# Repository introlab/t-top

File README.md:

# T-Top

T-Top is a tabletop robot designed with advanced audio and vision sensors, deep learning perceptual processing and
telecommunication capabilities to provide richer interaction modalities and develop higher cognitive abilities from
interacting with people.

## Authors

- Marc-Antoine Maheux (@mamaheux)
- Dominic Létourneau (@doumdi)
- Philippe Warren (@philippewarren)
- Mariam Fdil (@MariamFdil)
- [François Michaud](mailto:francois.michaud@usherbrooke.ca), ing., Ph.D.

## Contributors

- Ian-Mathieu Joly (@joli-1801)
- Charles Caya (@chcaya)
- Alexandre Filion (@alexfilion)

## Licensing

- Source code files: [GPLv3](LICENSE_SOURCE_CODE)
- Other files: [Creative Commons Attribution-NonCommercial-ShareAlike 4.0 International Public License](LICENSE_OTHER)

## Features

| Category         | Type              | Description                                                                                                                                                                                                                                             |
| ---------------- | ----------------- | ------------------------------------------------------------------------------------------------------------------------------------------------------------------------------------------------------------------------------------------------------- |
| Power            | Power Adapter     | 19 V                                                                                                                                                                                                                                                    |
|                  | Battery           | 1x [RRC2054-2](https://www.rrc-ps.com/en/battery-packs/standard-battery-packs/products/RRC2054-2)                                                                                                                                                       |
|                  | Battery Charger   | 1x [RRC-PMM240](https://www.rrc-ps.com/en/battery-packs/standard-battery-packs/products/RRC-PMM240)                                                                                                                                                     |
| Sensors          | Microphone Array  | 16x [xSoundsMicrophones](https://github.com/introlab/xSoundsMicrophones), 1x [16SoundsUSB](https://github.com/introlab/16SoundsUSB)                                                                                                                     |
|                  | RGB-D Camera      | 1x [Intel RealSense D435i](https://www.intelrealsense.com/depth-camera-d435i/)                                                                                                                                                                          |
|                  | Wide Angle Camera | 1x [Arducam AR0230](https://www.uctronics.com/arducam-1080p-hd-wide-angle-wdr-usb-camera-module-for-computer-2mp-1-2-7-cmos-ar0230-100-degree-mini-uvc-usb2-0-spy-webcam-board-with-3-3ft-1m-cable-for-windows-linux-mac-os-android.html)               |
|                  | Touchscreen       | 1x 7 inch 1024x600 capacitive touchscreen                                                                                                                                                                                                               |
|                  | Current/Voltage   | [INA220](https://www.ti.com/product/INA220)                                                                                                                                                                                                             |
|                  | Light Sensors     | 4x [Adafruit ALS-PT19 ](https://www.adafruit.com/product/2748)                                                                                                                                                                                          |
|                  | Buttons           | 4x buttons                                                                                                                                                                                                                                              |
| Actuators        | Stewart Platform  | Displacement range: ±3 cm (x, y and z), ±20° (x and y), ±30° (z). Motor: [Dynamixel XL430-W250](https://emanual.robotis.com/docs/en/dxl/x/xl430-w250/)                                                                                                  |                                                         |
|                  | Rotating Base     | Displacement range: illimited. Motor: [Dynamixel XL430-W250](https://emanual.robotis.com/docs/en/dxl/x/xl430-w250/)                                                                                                                                     |
|                  | Speakers          | 4x [Dayton Audio DMA45-8](https://www.daytonaudio.com/product/1613/dma45-8-1-1-2-dual-magnet-aluminum-cone-full-range-driver-8-ohm), 2x [MAX9744](https://www.adafruit.com/product/1752)                                                                |
|                  | Cooling           | 2x [Noctua NF-A4x20 5V](https://noctua.at/en/products/fan/nf-a4x20-5v)                                                                                                                                                                                  |
|                  | Touchscreen       | 1x 7 inch 1024x600 capacitive touchscreen                                                                                                                                                                                                               |
|                  | LED               | Battery status, volume level, led strip                                                                                                                                                                                                                 |
| Network          | WiFi              | Intel Dual Band Wireless-AC 8265 NGW                                                                                                                                                                                                                    |
|                  | Ethernet          | 100 Mbps                                                                                                                                                                                                                                                |
| Processing       | Computer          | [NVIDIA Jetson AGX Xavier Developer Kit](https://developer.nvidia.com/embedded/jetson-agx-xavier-developer-kit) or [NVIDIA Jetson AGX Xavier Orin Developer Kit](https://developer.nvidia.com/embedded/jetson-agx-orin-developer-kit)                   |
|                  | Motor MCU         | [Teensy 4.0](https://www.pjrc.com/store/teensy40.html)                                                                                                                                                                                                  |
|                  | Battery MCU       | [Teensy LC](https://www.pjrc.com/teensy/teensyLC.html)                                                                                                                                                                                                  |
| Perceptions      |                   | SLAM, object detection, person pose estimation, face recognition, sound classification, speaker identification, robot name detection, speech to text, person identification, music beat detection, source source localization, ego noise reduction, vad |
| Behaviors        |                   | Telepresence, emotions, talking, greeting, face following, dancing, exploring, sound following                                                                                                                                                          |

## Repository Structure

- The [documentation](documentation) folder contains the documentation to build and configure T-Top.
- The [CAD](CAD) folder contains the SolidWorks files of the robot. Il also contains the DXF and STL files to cut and
  print custom parts.
- The [firmwares](firmwares) folder contains the firmware for the MCUs.
- The [PCB](PCB) folder contains the KiCad files of the custom PCBs. Il also contains the Gerber files to manufacture
  the PCBs.
- The [ros](ros) folder contains the ROS packages to use the robot.
- The [tools](tools) folder contains the tools to develop and use the robot.

## Development Computer Setup

See [01_COMPUTER_CONFIGURATION.md](documentation/assembly/01_COMPUTER_CONFIGURATION.md#development-computer-ubuntu-2004)

## Papers

- [M.-A. Maheux, D. Létourneau, P. Warren, A. M. Panchea, J. M. Robillard and F. Michaud, “‍Designing a Tabletop SAR as an Advanced HRI Experimentation Platform,” in Proceedings of the 2024 International Symposium on Technological Advances in Human-Robot Interaction (TAHRI 2024), Boulder, CO, USA, 2024](https://dl.acm.org/doi/10.1145/3648536.3648538)
    - [YouTube Video](https://youtu.be/HSd65F055VE)
- [M. Fdil, M. Levasseur, D. Létourneau, M.-A. Maheux, M. Lussier-Therrien, F. Michaud, "Enhancing Open Conversations Using Visual Percepts From a Socially Assistive Robot -- Preliminary Assessment", in Proceedings of the International Conference on Social Robotics, 2024, pp. 1-12.](https://link.springer.com/chapter/10.1007/978-981-96-3519-1_17)
    - [YouTube Video](https://youtu.be/4ykoxQKUweU)  
- [A. M. Panchea, M.-A. Maheux, P. Warren, D. Létourneau and F. Michaud, “Exploratory Evaluation of a Tabletop Robot With Older Adults,” in Proceedings of the 2024 ACM/IEEE International Conference on Human-Robot Interaction, Boulder, CO, USA, 2024, pp. 817–821.](https://dl.acm.org/doi/10.1145/3610978.3640621)
- [M.-A. Maheux, A. M. Panchea, P. Warren, D. Létourneau and F. Michaud, “T-Top, an Open Source Tabletop Robot with Advanced Onboard Audio, Vision and Deep Learning Capabilities,” in Proceedings of the 2023 IEEE/RSJ International Conference on Intelligent Robots and Systems (IROS), Detroit, MI, USA, 2023, pp. 7862-7869.](https://ieeexplore.ieee.org/abstract/document/10342252)
- [M.-A. Maheux, C. Caya, D. Létourneau and F. Michaud, “T-Top, a sar experimental platform,” in Proceedings of the 2022 ACM/IEEE International Conference on Human-Robot Interaction, 2022, pp. 904–908.](https://dl.acm.org/doi/abs/10.5555/3523760.3523902)

## Sponsor

[IntRoLab - Intelligent / Interactive / Integrated / Interdisciplinary Robot Lab](https://introlab.3it.usherbrooke.ca)

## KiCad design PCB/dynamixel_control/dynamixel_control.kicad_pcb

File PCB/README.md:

# PCB
To build T-Top, two cutom PCBs must be made.

## Folder Structure
- The [psu_control](psu_control) folder contains the PCB files for the PCB that controls and monitors the battery, audio amplifier, fans and LEDs.
- The [dynamixel_control](dynamixel_control) folder contains the PCB files for the PCB that controls the Dynamixel motors.
- The [buck_boost](buck_boost) folder contains the PCB files for the Buck-Boost PCB.
- The [t-top.pretty](t-top.pretty) folder contains the custom footprints.
- The [t-top.kicad_sym](t-top.kicad_sym) file contains the custom parts.

## PSU Control PCB
- [Schematic](psu_control/schematic.pdf)
- [Gerber](psu_control/gerber)
- [Bill of Materials](../documentation/assembly/00_ORDER_PRINT_LASER_CUTTING.md#psu-control-pcb)

## Dynamixel Control PCB
- [Schematic](dynamixel_control/schematic.pdf)
- [Gerber](dynamixel_control/gerber)
- [Bill of Materials](../documentation/assembly/00_ORDER_PRINT_LASER_CUTTING.md#dynamixel-control-pcb)

## Buck-Boost PCB
- [Schematic](buck_boost/schematic.pdf)
- [Gerber](buck_boost/gerber)
- [Bill of Materials](../documentation/assembly/00_ORDER_PRINT_LASER_CUTTING.md#buck-boost-pcb)

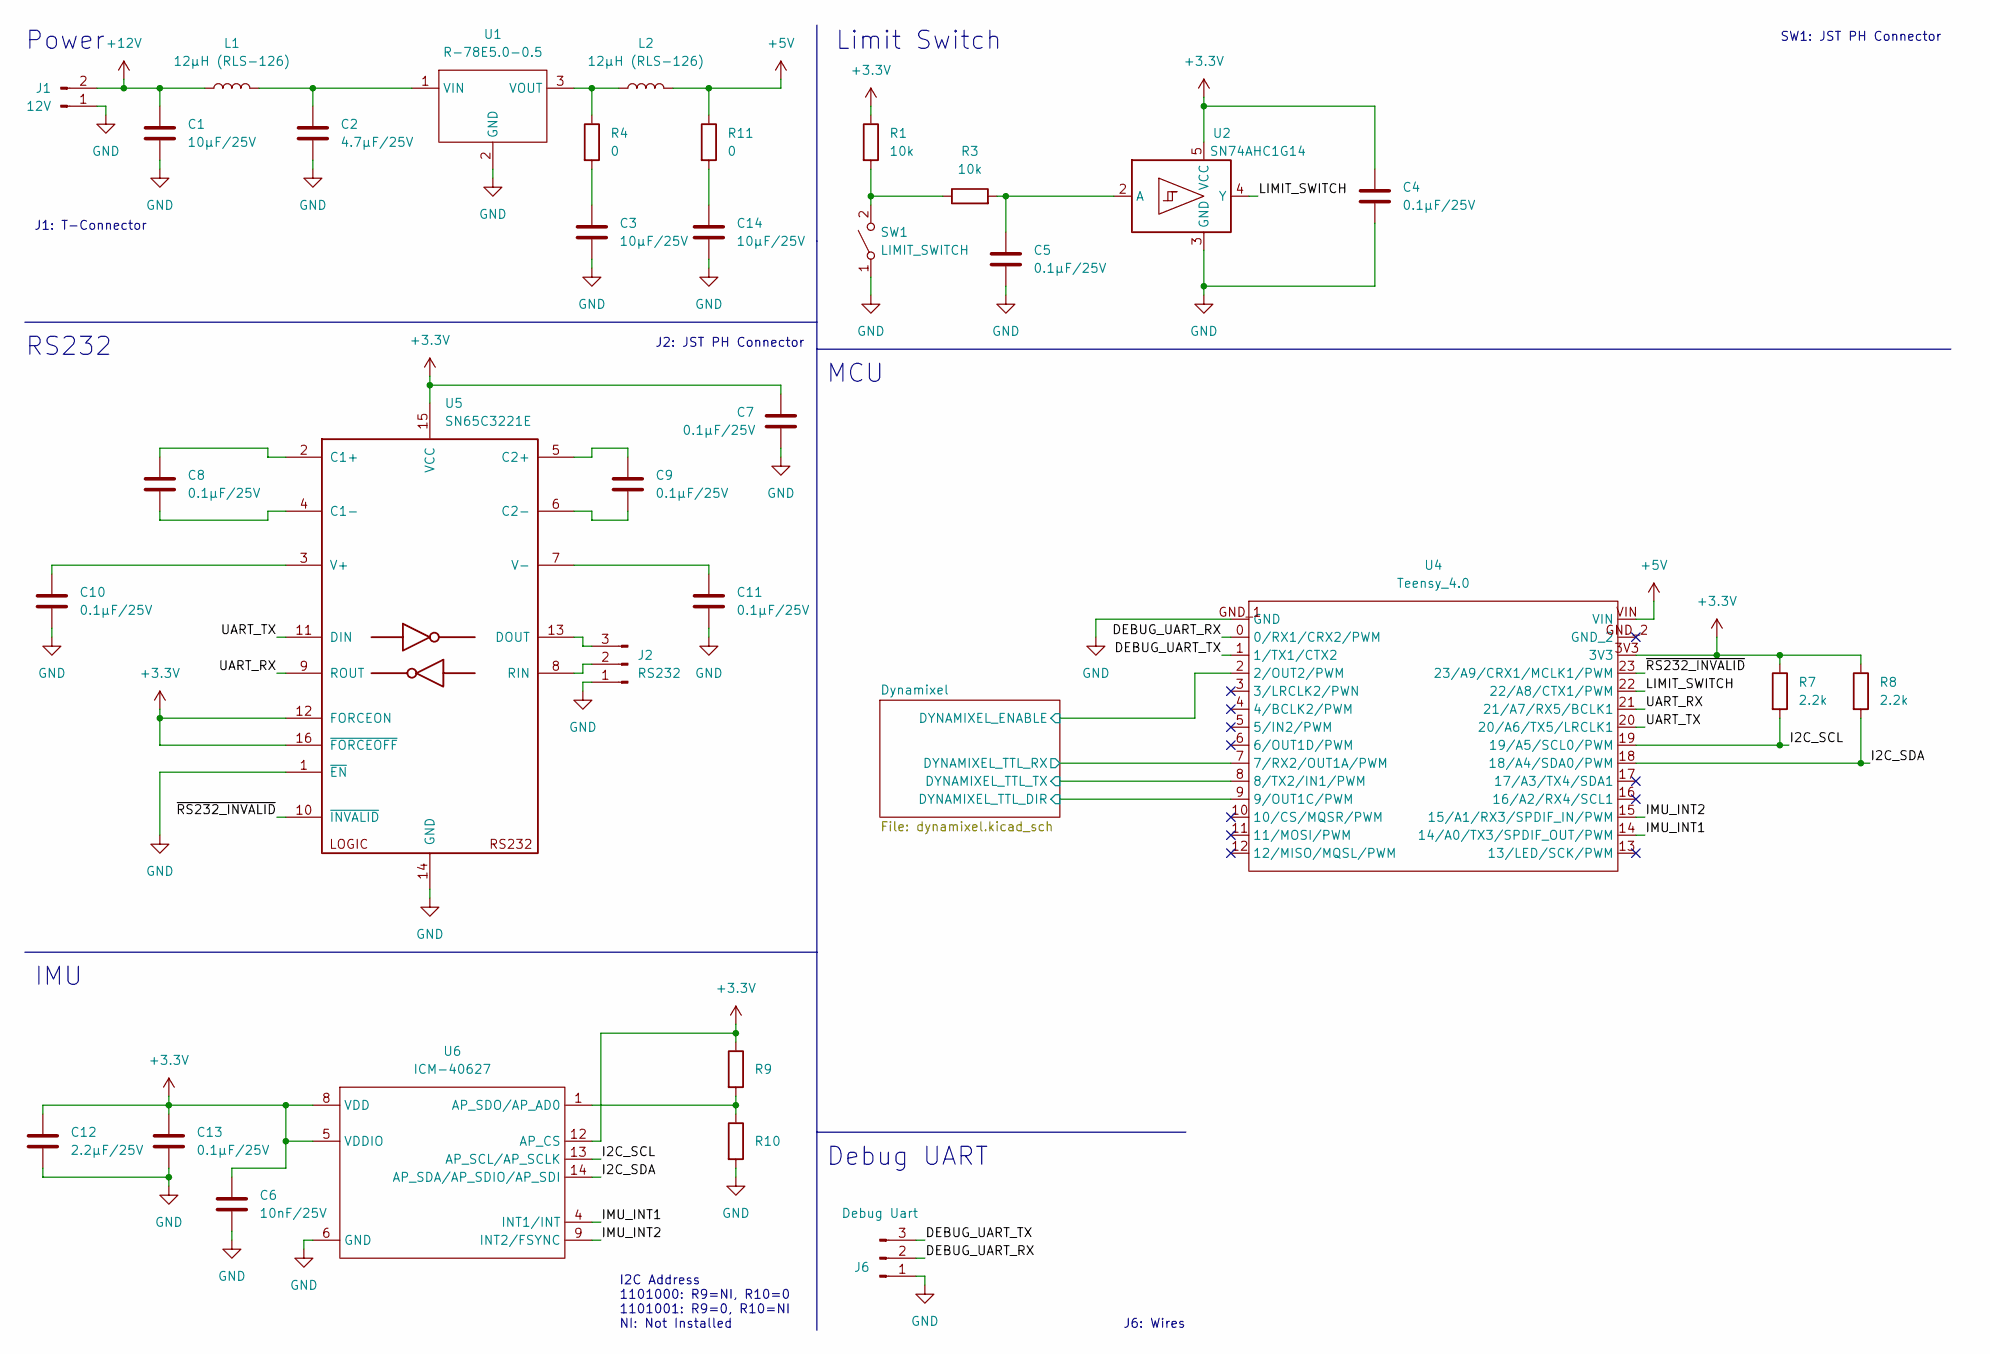
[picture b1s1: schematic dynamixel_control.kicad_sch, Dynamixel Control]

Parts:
C1, C3, C14: 10µF/25V; C_0805_2012Metric
C2: 4.7µF/25V; C_0805_2012Metric
C4, C5, C7, C8, C9, C10, C11, C13: 0.1µF/25V; C_0805_2012Metric
C6: 10nF/25V; C_0805_2012Metric
C12: 2.2µF/25V; C_0805_2012Metric
J1: 12V; t-connector
J2: RS232; JST_PH_S3B-PH-K_1x03_P2.00mm_Horizontal
J6: Debug Uart; PinHeader_1x03_P1.27mm_Vertical
L1, L2: 12µH (RLS-126); L_1812_4532Metric
R1, R3: 10k; R_0805_2012Metric
R4, R10, R11: 0; R_0805_2012Metric
R7, R8: 2.2k; R_0805_2012Metric
R9: NI; R_0805_2012Metric
SW1: LIMIT_SWITCH; JST_PH_B2B-PH-K_1x02_P2.00mm_Vertical
U1: R-78E5.0-0.5; R-78E-0.5
U2: SN74AHC1G14; SOT-23-5
U4: Teensy_4.0
U5: SN65C3221E; TSSOP-16_4.4x5mm_P0.65mm
U6: ICM-40627

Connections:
+3.3V: C4.1, C6.1, C7.1, C12.1, C13.1, R1.1, R7.1, R8.1, R9.1, U2.5 (VCC), U4.3V3, U5.12 (FORCEON), U5.15 (VCC), U5.16 (~FORCEOFF), U6.5 (VDDIO), U6.8 (VDD), U6.12 (AP_CS); also elsewhere on the board
+5V: L2.2, R11.1, U4.VIN; also elsewhere on the board
+12V: C1.1, J1.2, L1.1; also elsewhere on the board
/DEBUG_UART_RX: J6.2, U4.0 (0/RX1/CRX2/PWM)
/DEBUG_UART_TX: J6.3, U4.1 (1/TX1/CTX2)
/Dynamixel/DYNAMIXEL_ENABLE: U4.2 (2/OUT2/PWM); also elsewhere on the board
/Dynamixel/DYNAMIXEL_TTL_DIR: U4.9 (9/OUT1C/PWM); also elsewhere on the board
/Dynamixel/DYNAMIXEL_TTL_RX: U4.7 (7/RX2/OUT1A/PWM); also elsewhere on the board
/Dynamixel/DYNAMIXEL_TTL_TX: U4.8 (8/TX2/IN1/PWM); also elsewhere on the board
/I2C_SCL: R7.2, U4.19 (19/A5/SCL0/PWM), U6.13 (AP_SCL/AP_SCLK)
/I2C_SDA: R8.2, U4.18 (18/A4/SDA0/PWM), U6.14 (AP_SDA/AP_SDIO/AP_SDI)
/IMU_INT1: U4.14 (14/A0/TX3/SPDIF_OUT/PWM), U6.4 (INT1/INT)
/IMU_INT2: U4.15 (15/A1/RX3/SPDIF_IN/PWM), U6.9 (INT2/FSYNC)
/LIMIT_SWITCH: U2.4 (Y), U4.22 (22/A8/CTX1/PWM)
/UART_RX: U4.21 (21/A7/RX5/BCLK1), U5.9 (ROUT)
/UART_TX: U4.20 (20/A6/TX5/LRCLK1), U5.11 (DIN)
/~RS232_INVALID: U4.23 (23/A9/CRX1/MCLK1/PWM), U5.10 (~INVALID)
GND: C1.2, C2.2, C3.2, C4.2, C5.2, C6.2, C7.2, C10.2, C11.2, C12.2, C13.2, C14.2, J1.1, J2.1, J6.1, R10.2, SW1.1 (A), U1.2 (GND), U2.3 (GND), U4.GND_1 (GND), U5.1 (~EN), U5.14 (GND), U6.6 (GND); also elsewhere on the board
unnamed: C2.1, L1.2, U1.1 (VIN)
unnamed: C3.1, R4.2
unnamed: C5.1, R3.2, U2.2 (A)
unnamed: C8.1, U5.2 (C1+)
unnamed: C8.2, U5.4 (C1-)
unnamed: C9.1, U5.5 (C2+)
unnamed: C9.2, U5.6 (C2-)
unnamed: C10.1, U5.3 (V+)
unnamed: C11.1, U5.7 (V-)
unnamed: C14.1, R11.2
unnamed: J2.2, U5.8 (RIN)
unnamed: J2.3, U5.13 (DOUT)
unnamed: L2.1, R4.1, U1.3 (VOUT)
unnamed: R1.2, R3.1, SW1.2 (B)
unnamed: R9.2, R10.1, U6.1 (AP_SDO/AP_AD0)

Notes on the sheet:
SW1: JST PH Connector
J2: JST PH Connector
RS232
Limit Switch
J6: Wires
IMU
J1: T-Connector
Debug UART
Power
MCU
I2C Address 1101000: R9=NI, R10=0 1101001: R9=0, R10=NI NI: Not Installed

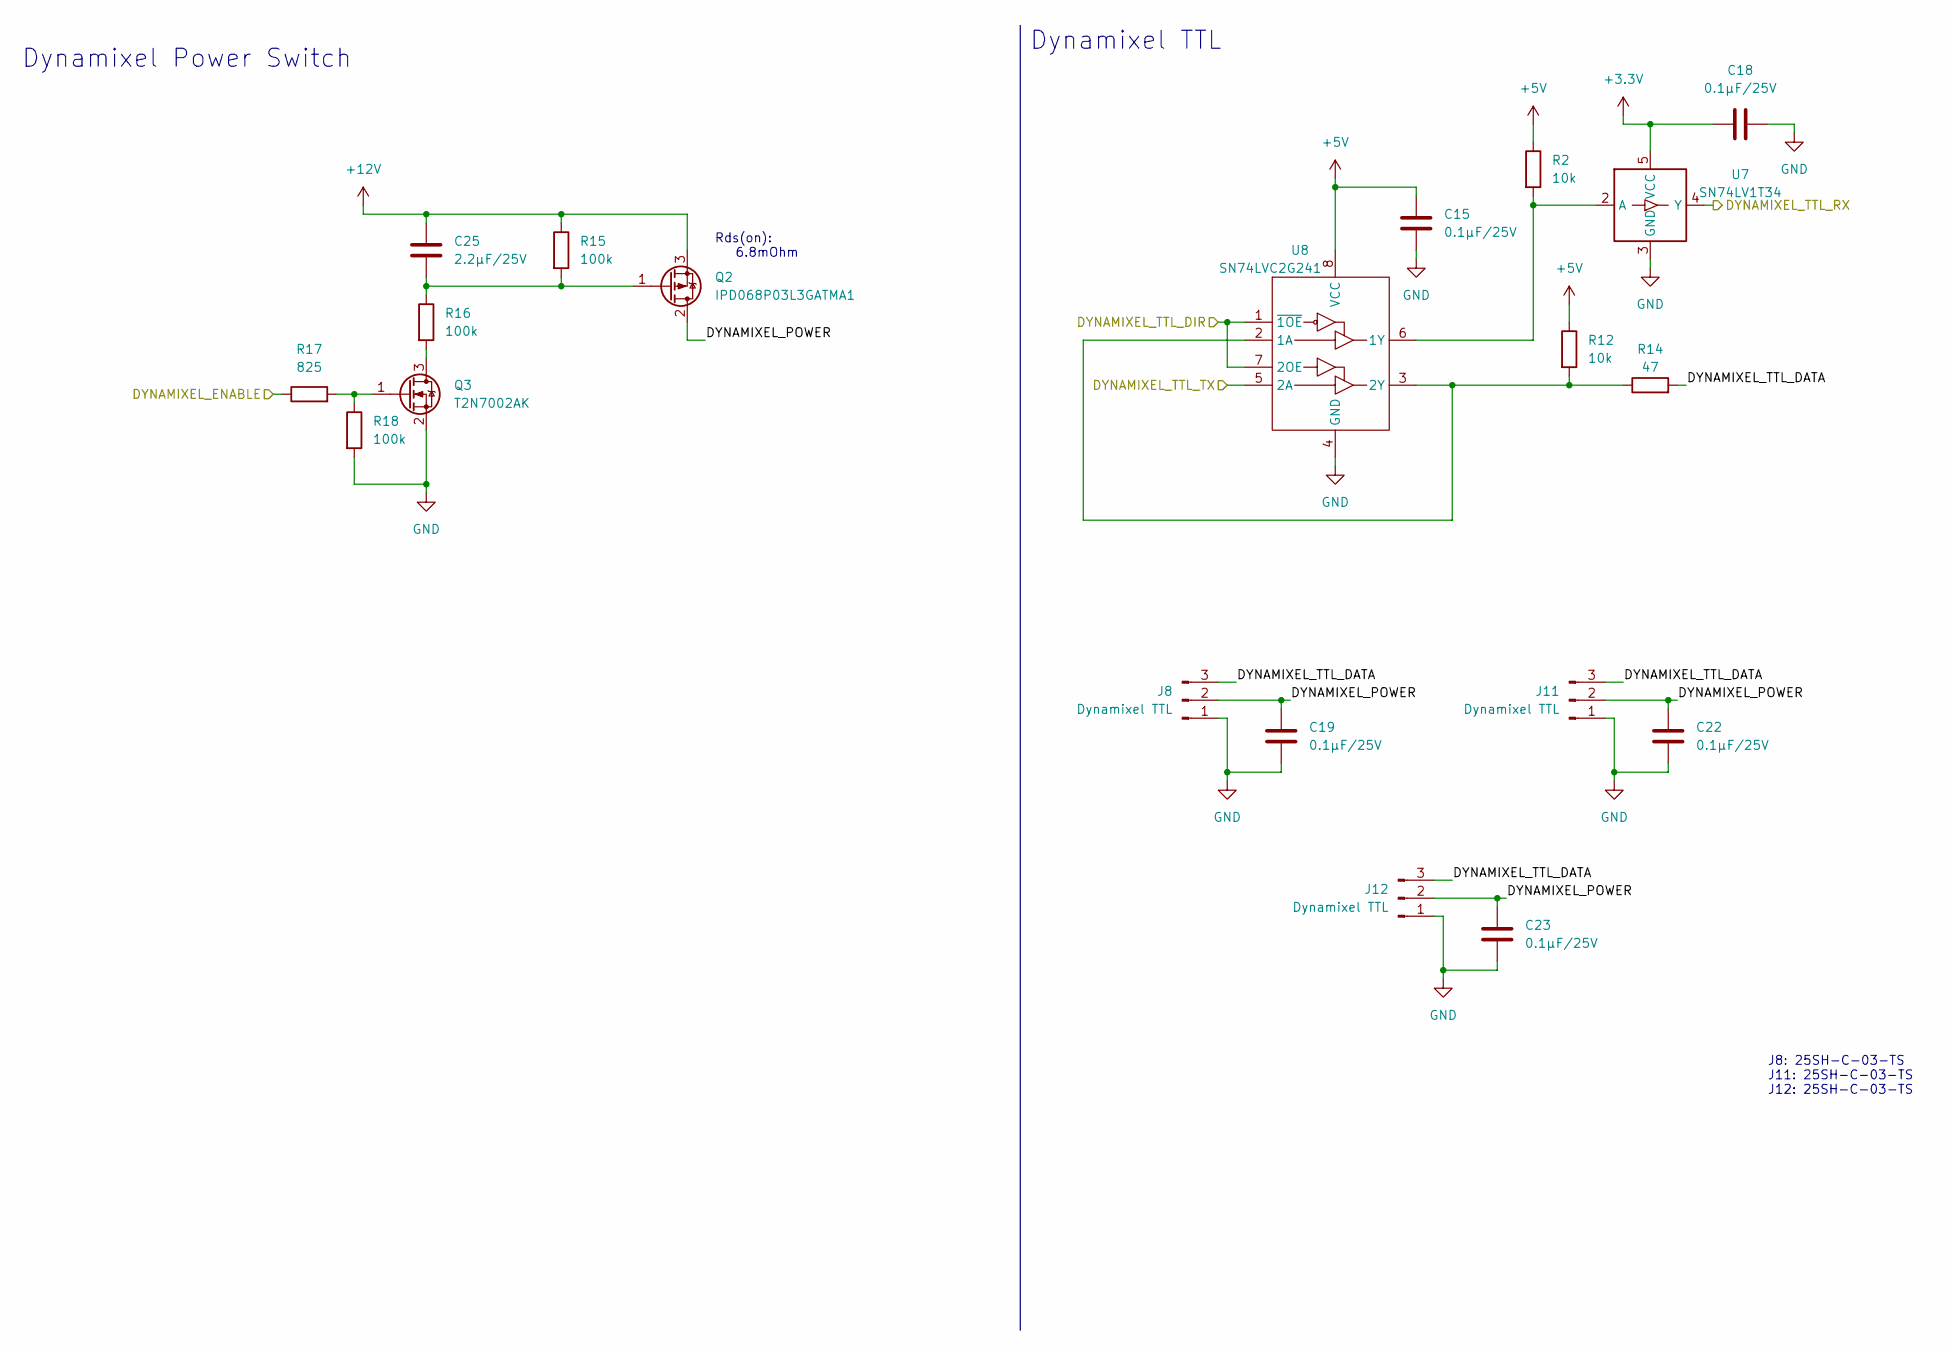
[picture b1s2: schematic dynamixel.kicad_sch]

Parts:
C15, C18, C19, C22, C23: 0.1µF/25V; C_0805_2012Metric
C25: 2.2µF/25V; C_0805_2012Metric
J8, J11, J12: Dynamixel TTL; 25SH-C-03-TS
Q2: IPD068P03L3GATMA1; TO-252-2
Q3: T2N7002AK; SOT-23
R2, R12: 10k; R_0805_2012Metric
R14: 47; R_0805_2012Metric
R15, R16, R18: 100k; R_0805_2012Metric
R17: 825; R_0805_2012Metric
U7: SN74LV1T34; SOT-23-5
U8: SN74LVC2G241; VSSOP-8_2.3x2mm_P0.5mm

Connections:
+3.3V: C18.1, U7.5 (VCC); also elsewhere on the board
+5V: C15.1, R2.1, R12.1, U8.8 (VCC); also elsewhere on the board
+12V: C25.1, Q2.3 (S), R15.1; also elsewhere on the board
/Dynamixel/DYNAMIXEL_ENABLE: R17.1; also elsewhere on the board
/Dynamixel/DYNAMIXEL_POWER: C19.1, C22.1, C23.1, J8.2, J11.2, J12.2, Q2.2 (D)
/Dynamixel/DYNAMIXEL_TTL_DATA: J8.3, J11.3, J12.3, R14.2
/Dynamixel/DYNAMIXEL_TTL_DIR: U8.1 (~1OE), U8.7 (2OE); also elsewhere on the board
/Dynamixel/DYNAMIXEL_TTL_RX: U7.4 (Y); also elsewhere on the board
/Dynamixel/DYNAMIXEL_TTL_TX: U8.5 (2A); also elsewhere on the board
GND: C15.2, C18.2, C19.2, C22.2, C23.2, J8.1, J11.1, J12.1, Q3.2 (S), R18.2, U7.3 (GND), U8.4 (GND); also elsewhere on the board
unnamed: C25.2, Q2.1 (G), R15.2, R16.1
unnamed: Q3.1 (G), R17.2, R18.1
unnamed: Q3.3 (D), R16.2
unnamed: R2.2, U7.2 (A), U8.6 (1Y)
unnamed: R12.2, R14.1, U8.2 (1A), U8.3 (2Y)

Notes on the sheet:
J8: 25SH-C-03-TS J11: 25SH-C-03-TS J12: 25SH-C-03-TS
Rds(on): 6.8mOhm
Dynamixel Power Switch
Dynamixel TTL

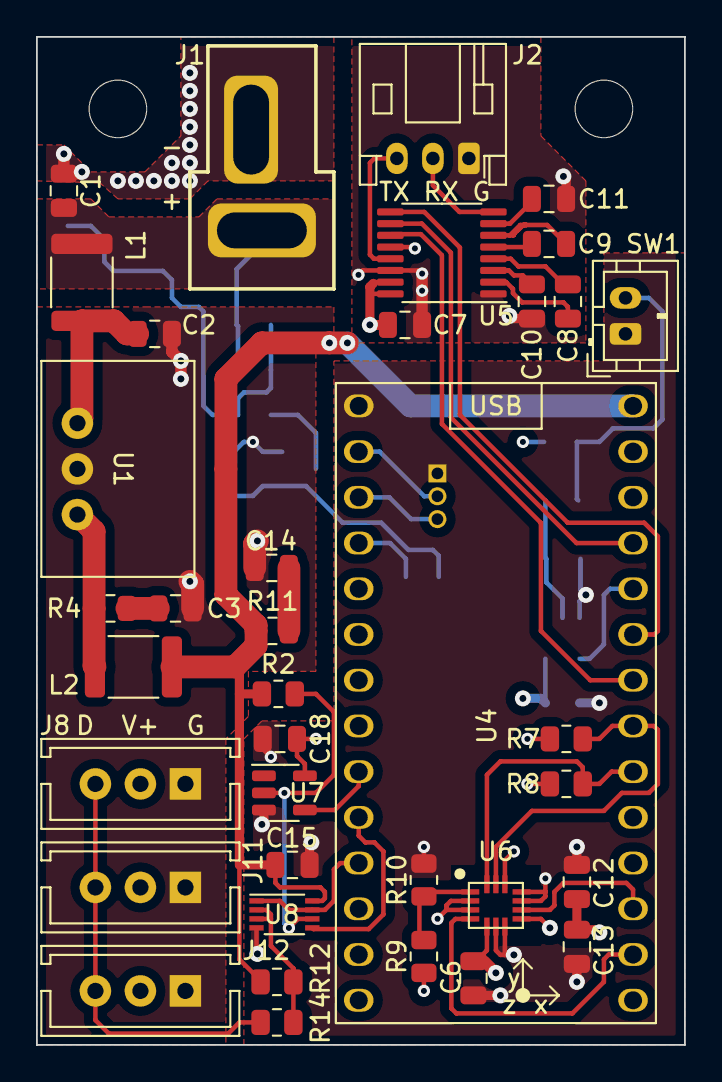
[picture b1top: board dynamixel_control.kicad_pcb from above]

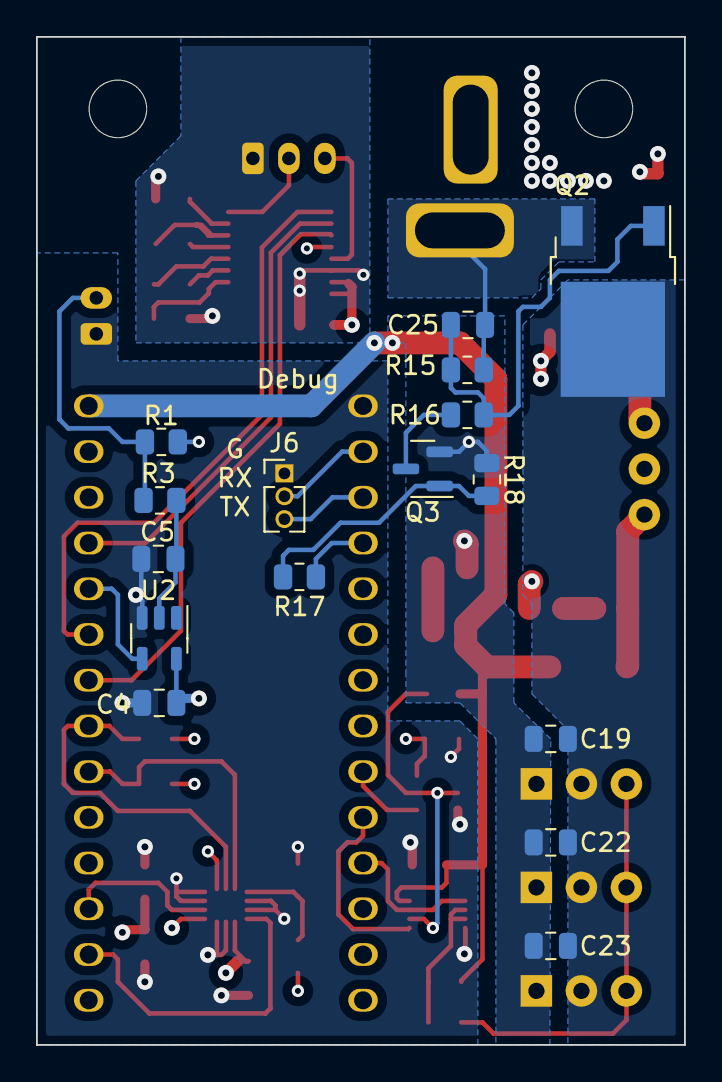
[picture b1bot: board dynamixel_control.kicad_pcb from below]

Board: 4 copper layers, 36.0 x 56.0 mm, 54 parts (16 on the bottom side), 40 nets.

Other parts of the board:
MH1: MountingHole_3.2mm_M3

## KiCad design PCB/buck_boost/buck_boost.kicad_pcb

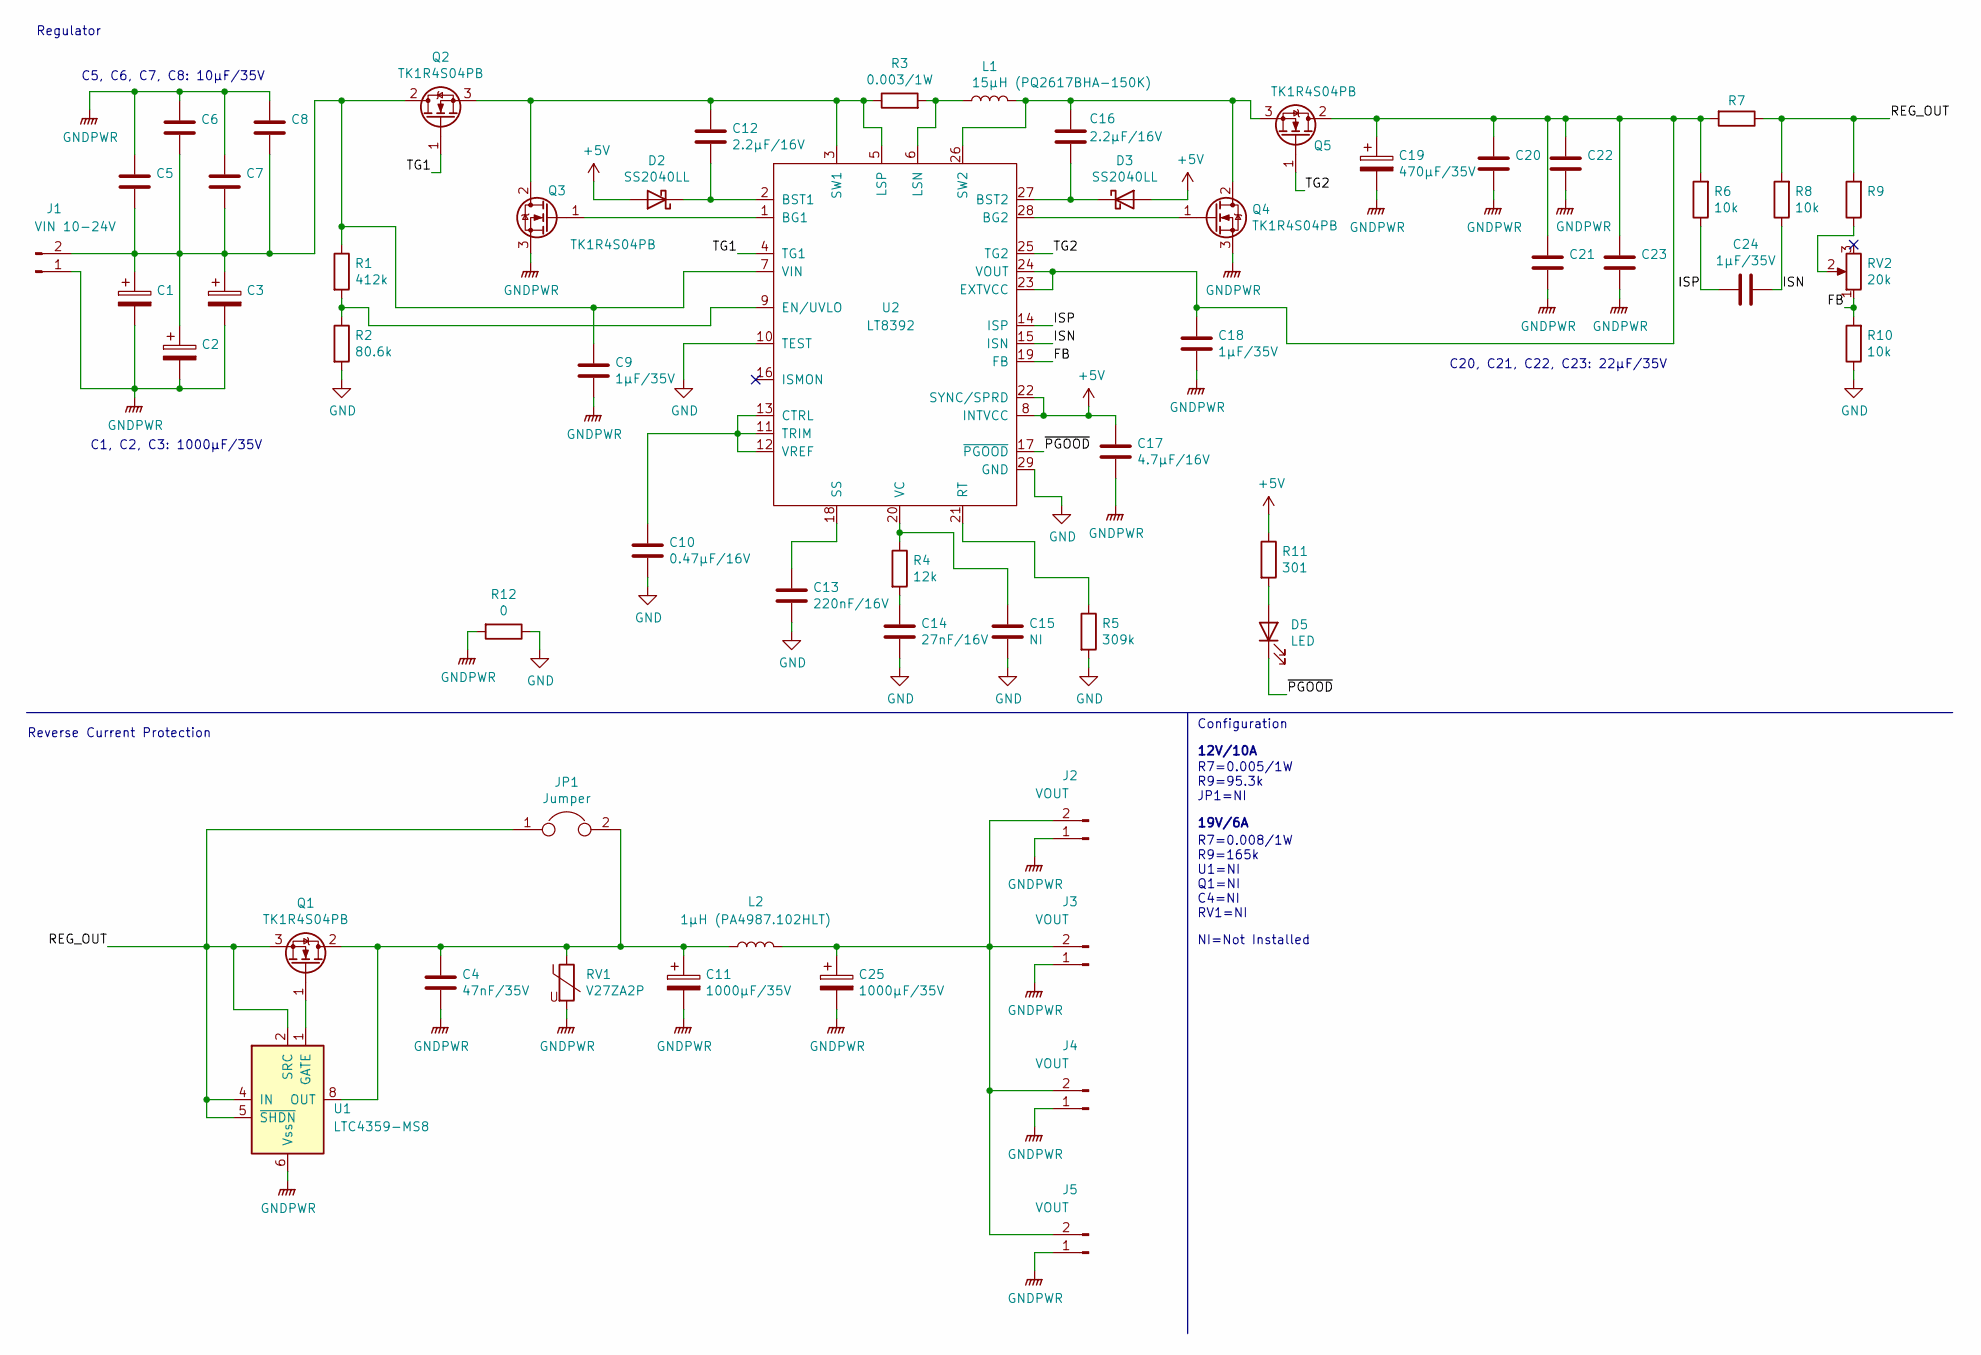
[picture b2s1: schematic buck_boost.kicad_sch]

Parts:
C1, C2, C3, C11, C25: 1000µF/35V; CP_Radial_D12.5mm_P5.00mm
C4: 47nF/35V; C_0805_2012Metric
C5, C6, C7, C8: 10µF/35V; C_1206_3216Metric
C9, C18, C24: 1µF/35V; C_0805_2012Metric
C10: 0.47µF/16V; C_0805_2012Metric
C12, C16: 2.2µF/16V; C_0805_2012Metric
C13: 220nF/16V; C_0805_2012Metric
C14: 27nF/16V; C_0805_2012Metric
C15: NI; C_0805_2012Metric
C17: 4.7µF/16V; C_0805_2012Metric
C19: 470µF/35V; CP_Radial_D12.5mm_P5.00mm
C20, C21, C22, C23: 22µF/35V; C_1206_3216Metric
D2, D3: SS2040LL; D_SOD-123F
D5: LED; D_0805_2012Metric
J1: VIN 10-24V; OSTTA020161
J2, J3, J4, J5: VOUT; OSTTA020161
JP1: Jumper; R_1206_3216Metric
L1: 15µH (PQ2617BHA-150K); PQ2617BHA-150K
L2: 1µH (PA4987.102HLT); PA4987.XXXHL
Q1, Q2, Q3, Q4, Q5: TK1R4S04PB; TO-252-2
R1: 412k; R_0805_2012Metric
R2: 80.6k; R_0805_2012Metric
R3: 0.003/1W; R_1206_3216Metric
R4: 12k; R_0805_2012Metric
R5: 309k; R_0805_2012Metric
R6, R8, R10: 10k; R_0805_2012Metric
R7: RIS; R_1206_3216Metric
R9: FB3; R_0805_2012Metric
R11: 301; R_0805_2012Metric
R12: 0; R_1206_3216Metric
RV1: V27ZA2P; RV_Disc_D12mm_W4.2mm_P7.5mm
RV2: 20k; Potentiometer_Bourns_3296W_Vertical
U1: LTC4359-MS8; MSOP-8_3x3mm_P0.65mm
U2: LT8392; TSSOP-28-1EP_4.4x9.7mm_P0.65mm

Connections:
+5V: C17.1, D2.2 (A), D3.2 (A), R11.1, U2.8 (INTVCC), U2.22 (SYNC/SPRD)
/FB: R10.2, RV2.1, U2.19 (FB)
/ISN: C24.1, R8.1, U2.15 (ISN)
/ISP: C24.2, R6.1, U2.14 (ISP)
/REG_OUT: JP1.1, Q1.3 (S), R7.1, R8.2, R9.2, U1.2 (SRC), U1.4 (IN), U1.5 (~SHDN)
/TG1: Q2.1 (G), U2.4 (TG1)
/TG2: Q5.1 (G), U2.25 (TG2)
/~PGOOD: D5.1 (K), U2.17 (~PGOOD)
GND: C10.2, C13.2, C14.2, C15.2, R2.2, R5.2, R10.1, R12.1, U2.10 (TEST), U2.29 (GND)
GNDPWR: C1.2, C2.2, C3.2, C4.2, C5.1, C6.1, C7.1, C8.1, C9.2, C11.2, C17.2, C18.2, C19.2, C20.2, C21.2, C22.2, C23.2, C25.2, J1.1, J2.1, J3.1, J4.1, J5.1, Q3.3 (S), Q4.3 (S), R12.2, RV1.2, U1.6 (Vss)
unnamed: C1.1, C2.1, C3.1, C5.2, C6.2, C7.2, C8.2, C9.1, J1.2, Q2.2 (D), R1.1, U2.7 (VIN)
unnamed: C10.1, U2.11 (TRIM), U2.12 (VREF), U2.13 (CTRL)
unnamed: C4.1, C11.1, JP1.2, L2.1, Q1.2 (D), RV1.1, U1.8 (OUT)
unnamed: C12.1, Q2.3 (S), Q3.2 (D), R3.1, U2.3 (SW1), U2.5 (LSP)
unnamed: C12.2, D2.1 (K), U2.2 (BST1)
unnamed: C13.1, U2.18 (SS)
unnamed: C14.1, R4.2
unnamed: C15.1, R4.1, U2.20 (VC)
unnamed: C16.1, L1.2, Q4.2 (D), Q5.3 (S), U2.26 (SW2)
unnamed: C16.2, D3.1 (K), U2.27 (BST2)
unnamed: C18.1, C19.1, C20.1, C21.1, C22.1, C23.1, Q5.2 (D), R6.2, R7.2, U2.23 (EXTVCC), U2.24 (VOUT)
unnamed: C25.1, J2.2, J3.2, J4.2, J5.2, L2.2
unnamed: D5.2 (A), R11.2
unnamed: L1.1, R3.2, U2.6 (LSN)
unnamed: Q1.1 (G), U1.1 (GATE)
unnamed: Q3.1 (G), U2.1 (BG1)
unnamed: Q4.1 (G), U2.28 (BG2)
unnamed: R1.2, R2.1, U2.9 (EN/UVLO)
unnamed: R5.1, U2.21 (RT)
unnamed: R9.1, RV2.2

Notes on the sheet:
NI=Not Installed
12V/10A
Configuration
Regulator
C5, C6, C7, C8: 10µF/35V
R7=0.005/1W R9=95.3k JP1=NI
Reverse Current Protection
C20, C21, C22, C23: 22µF/35V
R7=0.008/1W R9=165k U1=NI Q1=NI C4=NI RV1=NI
19V/6A
C1, C2, C3: 1000µF/35V

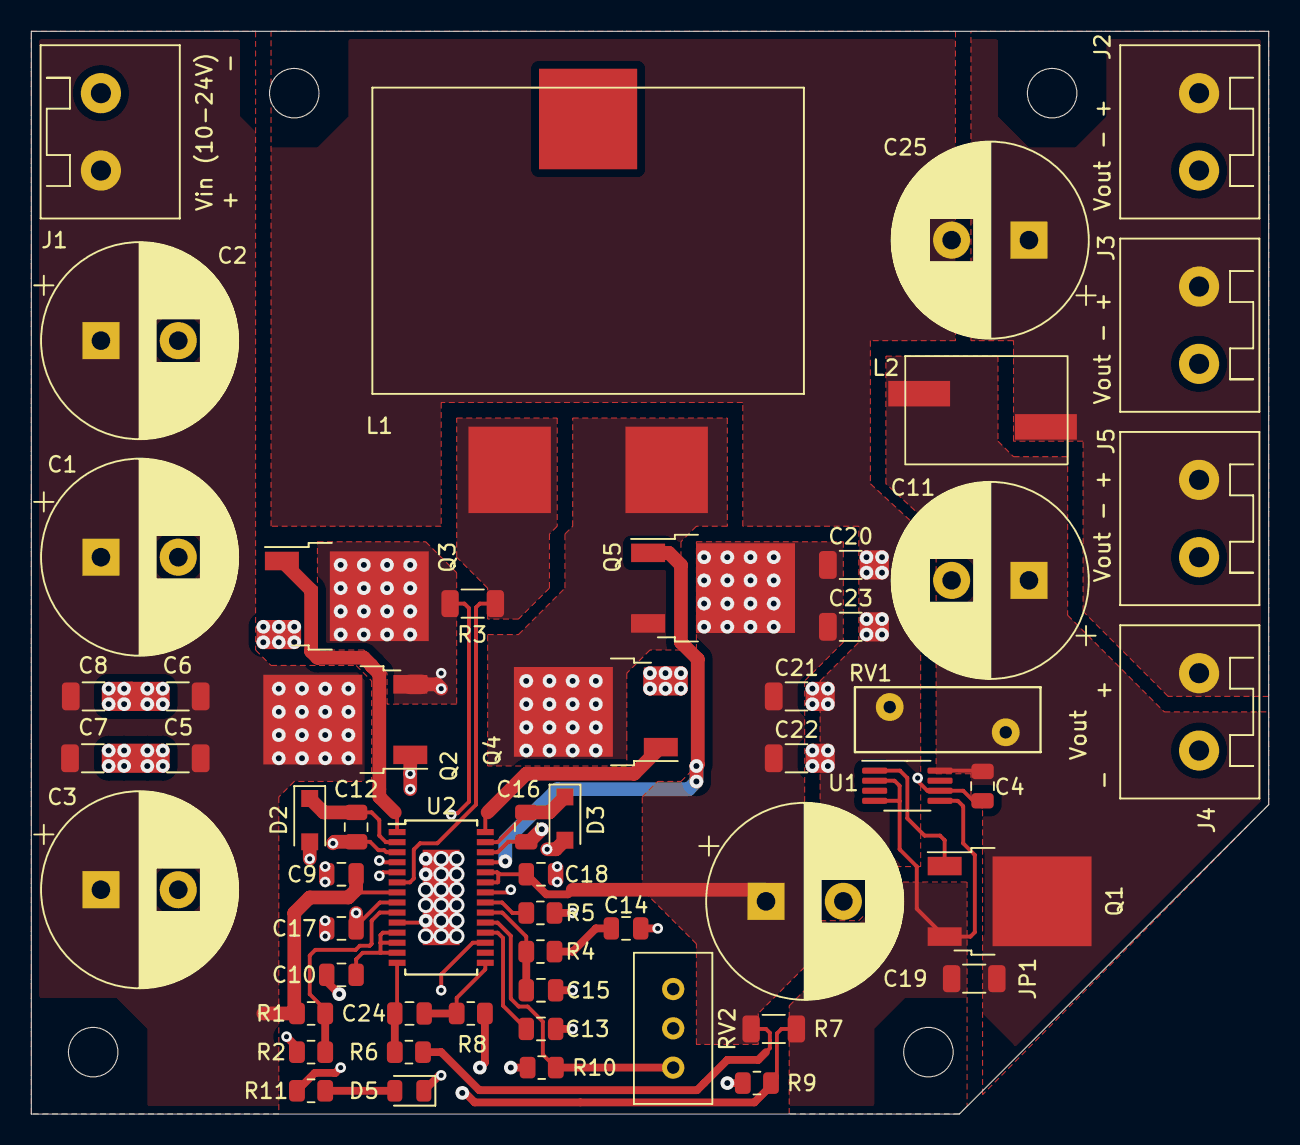
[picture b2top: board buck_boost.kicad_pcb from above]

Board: 4 copper layers, 80.0 x 70.0 mm, 57 parts (1 on the bottom side), 30 nets.

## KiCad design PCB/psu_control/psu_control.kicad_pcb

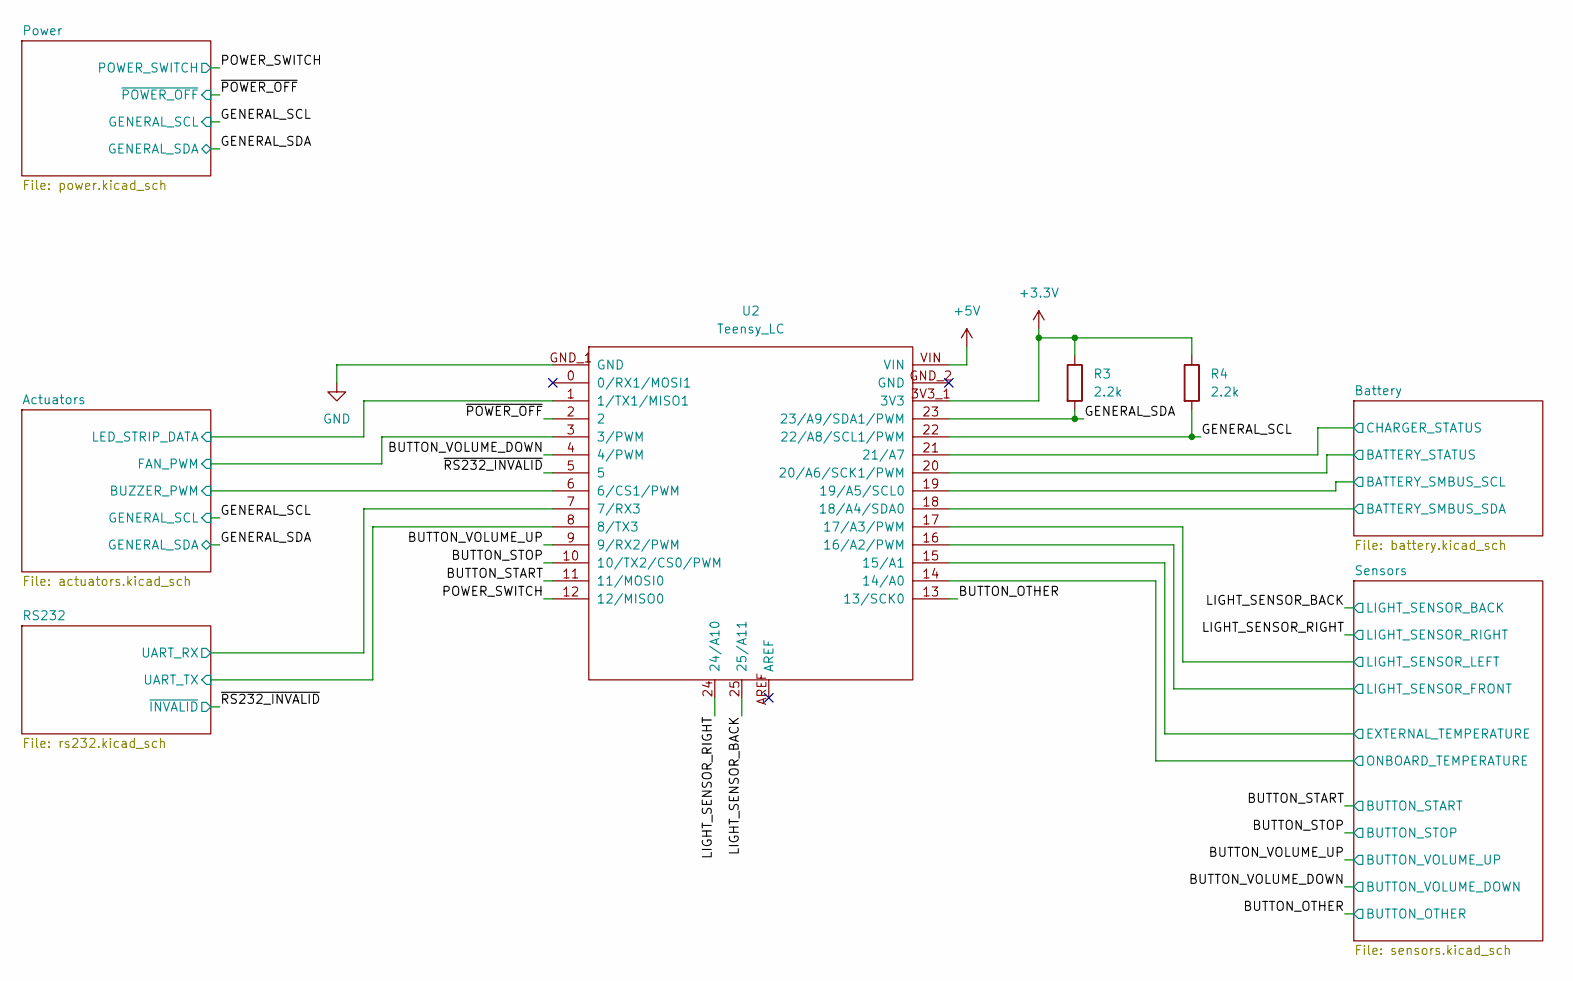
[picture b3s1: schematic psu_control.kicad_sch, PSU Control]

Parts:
R3, R4: 2.2k; R_0805_2012Metric
U2: Teensy_LC

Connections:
+3.3V: R3.1, R4.1, U2.3V3_1 (3V3); also elsewhere on the board
+5V: U2.VIN; also elsewhere on the board
/Actuators/BUZZER_PWM: U2.6 (6/CS1/PWM); also elsewhere on the board
/Actuators/FAN_PWM: U2.3 (3/PWM); also elsewhere on the board
/Actuators/LED_STRIP_DATA: U2.1 (1/TX1/MISO1); also elsewhere on the board
/BUTTON_OTHER: U2.13 (13/SCK0); also elsewhere on the board
/BUTTON_START: U2.11 (11/MOSI0); also elsewhere on the board
/BUTTON_STOP: U2.10 (10/TX2/CS0/PWM); also elsewhere on the board
/BUTTON_VOLUME_DOWN: U2.4 (4/PWM); also elsewhere on the board
/BUTTON_VOLUME_UP: U2.9 (9/RX2/PWM); also elsewhere on the board
/Battery/BATTERY_SMBUS_SCL: U2.19 (19/A5/SCL0); also elsewhere on the board
/Battery/BATTERY_SMBUS_SDA: U2.18 (18/A4/SDA0); also elsewhere on the board
/Battery/BATTERY_STATUS: U2.20 (20/A6/SCK1/PWM); also elsewhere on the board
/Battery/CHARGER_STATUS: U2.21 (21/A7); also elsewhere on the board
/GENERAL_SCL: R4.2, U2.22 (22/A8/SCL1/PWM); also elsewhere on the board
/GENERAL_SDA: R3.2, U2.23 (23/A9/SDA1/PWM); also elsewhere on the board
/LIGHT_SENSOR_BACK: U2.25 (25/A11); also elsewhere on the board
/LIGHT_SENSOR_RIGHT: U2.24 (24/A10); also elsewhere on the board
/POWER_SWITCH: U2.12 (12/MISO0); also elsewhere on the board
/RS232/UART_RX: U2.7 (7/RX3); also elsewhere on the board
/RS232/UART_TX: U2.8 (8/TX3); also elsewhere on the board
/Sensors/EXTERNAL_TEMPERATURE: U2.15 (15/A1); also elsewhere on the board
/Sensors/LIGHT_SENSOR_FRONT: U2.16 (16/A2/PWM); also elsewhere on the board
/Sensors/LIGHT_SENSOR_LEFT: U2.17 (17/A3/PWM); also elsewhere on the board
/Sensors/ONBOARD_TEMPERATURE: U2.14 (14/A0); also elsewhere on the board
/~POWER_OFF: U2.2; also elsewhere on the board
/~RS232_INVALID: U2.5; also elsewhere on the board
GND: U2.GND_1 (GND); also elsewhere on the board
